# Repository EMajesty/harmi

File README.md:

Continuation of [arduchord](https://github.com/EMajesty/arduchord), now using a Raspberry Pi Pico

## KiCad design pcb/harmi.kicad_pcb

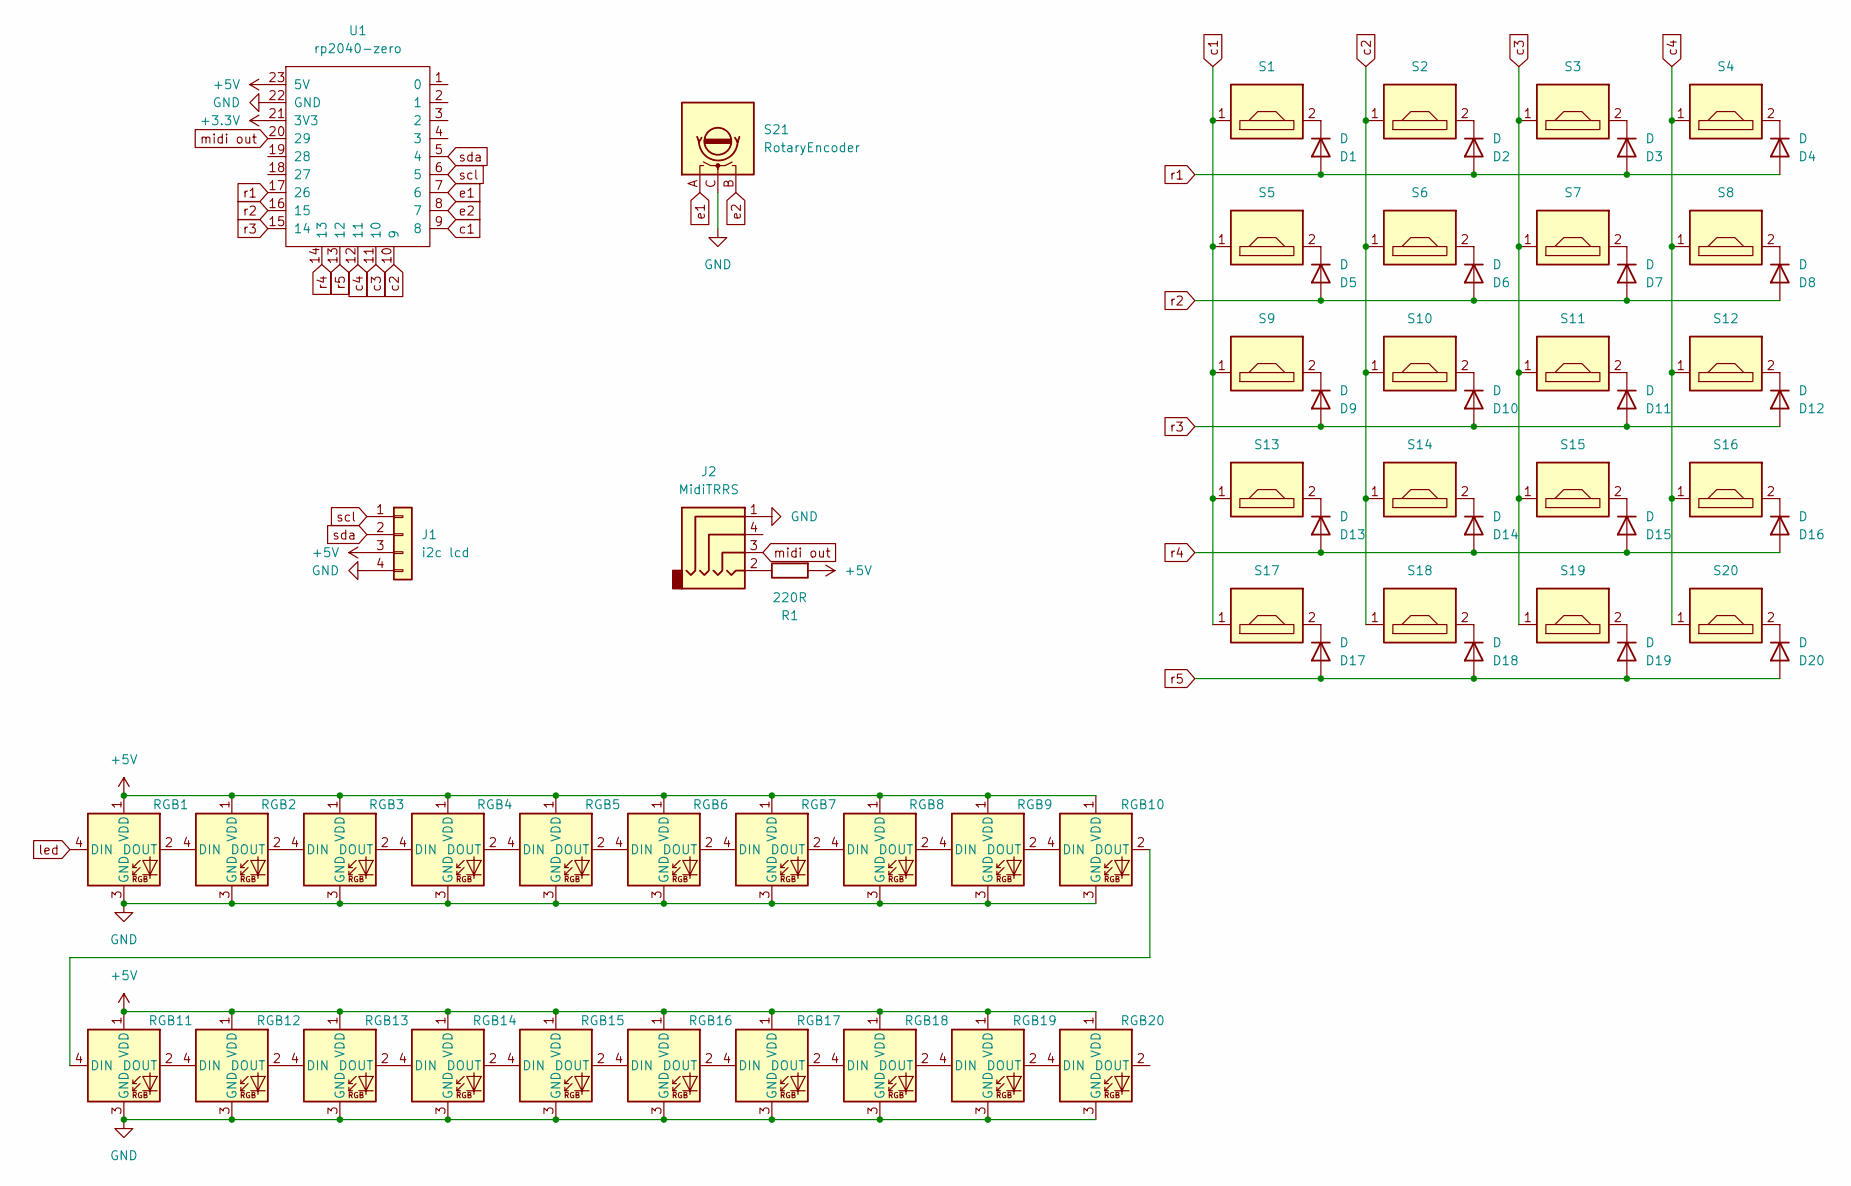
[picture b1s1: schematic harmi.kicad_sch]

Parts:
D1, D2, D3, D4, D5, D6, D7, D8, D9, D10, D11, D12, D13, D14, D15, D16, D17, D18, D19, D20: D; Diode-Hybrid-Back
J1: i2c lcd; PinHeader_1x04_P2.54mm_Horizontal
J2: MidiTRRS; TRRS-PJ-320A
R1: 220R; Resistor-Hybrid-Back
RGB1, RGB2, RGB3, RGB4, RGB5, RGB6, RGB7, RGB8, RGB9, RGB10, RGB11, RGB12, RGB13, RGB14, RGB15, RGB16, RGB17, RGB18, RGB19, RGB20: SK6812MINI-E
S1, S2, S3, S4, S5, S6, S7, S8, S9, S10, S11, S12, S13, S14, S15, S16, S17, S18, S19, S20: PG1350
S21: RotaryEncoder; RotaryEncoder_Bourns_Vertical_PEC12R-3x17F-Nxxxx
U1: rp2040-zero; rp2040-zero-tht

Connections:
+3.3V: U1.21 (3V3)
+5V: J1.3, R1.2, RGB1.1 (VDD), RGB2.1 (VDD), RGB3.1 (VDD), RGB4.1 (VDD), RGB5.1 (VDD), RGB6.1 (VDD), RGB7.1 (VDD), RGB8.1 (VDD), RGB9.1 (VDD), RGB10.1 (VDD), RGB11.1 (VDD), RGB12.1 (VDD), RGB13.1 (VDD), RGB14.1 (VDD), RGB15.1 (VDD), RGB16.1 (VDD), RGB17.1 (VDD), RGB18.1 (VDD), RGB19.1 (VDD), RGB20.1 (VDD), U1.23 (5V)
GND: J1.4, J2.1, RGB1.3 (GND), RGB2.3 (GND), RGB3.3 (GND), RGB4.3 (GND), RGB5.3 (GND), RGB6.3 (GND), RGB7.3 (GND), RGB8.3 (GND), RGB9.3 (GND), RGB10.3 (GND), RGB11.3 (GND), RGB12.3 (GND), RGB13.3 (GND), RGB14.3 (GND), RGB15.3 (GND), RGB16.3 (GND), RGB17.3 (GND), RGB18.3 (GND), RGB19.3 (GND), RGB20.3 (GND), S21.C, U1.22 (GND)
unnamed: D1.1 (K), S1.2
unnamed: D2.1 (K), S2.2
unnamed: D3.1 (K), S3.2
unnamed: D4.1 (K), S4.2
unnamed: D5.1 (K), S5.2
unnamed: D6.1 (K), S6.2
unnamed: D7.1 (K), S7.2
unnamed: D8.1 (K), S8.2
unnamed: D9.1 (K), S9.2
unnamed: D10.1 (K), S10.2
unnamed: D11.1 (K), S11.2
unnamed: D12.1 (K), S12.2
unnamed: D13.1 (K), S13.2
unnamed: D14.1 (K), S14.2
unnamed: D15.1 (K), S15.2
unnamed: D16.1 (K), S16.2
unnamed: D17.1 (K), S17.2
unnamed: D18.1 (K), S18.2
unnamed: D19.1 (K), S19.2
unnamed: D20.1 (K), S20.2
unnamed: J2.2, R1.1
unnamed: RGB1.2 (DOUT), RGB2.4 (DIN)
unnamed: RGB2.2 (DOUT), RGB3.4 (DIN)
unnamed: RGB3.2 (DOUT), RGB4.4 (DIN)
unnamed: RGB4.2 (DOUT), RGB5.4 (DIN)
unnamed: RGB5.2 (DOUT), RGB6.4 (DIN)
unnamed: RGB6.2 (DOUT), RGB7.4 (DIN)
unnamed: RGB7.2 (DOUT), RGB8.4 (DIN)
unnamed: RGB8.2 (DOUT), RGB9.4 (DIN)
unnamed: RGB9.2 (DOUT), RGB10.4 (DIN)
unnamed: RGB10.2 (DOUT), RGB11.4 (DIN)
unnamed: RGB11.2 (DOUT), RGB12.4 (DIN)
unnamed: RGB12.2 (DOUT), RGB13.4 (DIN)
unnamed: RGB13.2 (DOUT), RGB14.4 (DIN)
unnamed: RGB14.2 (DOUT), RGB15.4 (DIN)
unnamed: RGB15.2 (DOUT), RGB16.4 (DIN)
unnamed: RGB16.2 (DOUT), RGB17.4 (DIN)
unnamed: RGB17.2 (DOUT), RGB18.4 (DIN)
unnamed: RGB18.2 (DOUT), RGB19.4 (DIN)
unnamed: RGB19.2 (DOUT), RGB20.4 (DIN)
c1: S1.1, S5.1, S9.1, S13.1, S17.1, U1.9 (8)
c2: S2.1, S6.1, S10.1, S14.1, S18.1, U1.10 (9)
c3: S3.1, S7.1, S11.1, S15.1, S19.1, U1.11 (10)
c4: S4.1, S8.1, S12.1, S16.1, S20.1, U1.12 (11)
e1: S21.A, U1.7 (6)
e2: S21.B, U1.8 (7)
led: RGB1.4 (DIN)
midi out: J2.3, U1.20 (29)
r1: D1.2 (A), D2.2 (A), D3.2 (A), D4.2 (A), U1.17 (26)
r2: D5.2 (A), D6.2 (A), D7.2 (A), D8.2 (A), U1.16 (15)
r3: D9.2 (A), D10.2 (A), D11.2 (A), D12.2 (A), U1.15 (14)
r4: D13.2 (A), D14.2 (A), D15.2 (A), D16.2 (A), U1.14 (13)
r5: D17.2 (A), D18.2 (A), D19.2 (A), D20.2 (A), U1.13 (12)
scl: J1.1, U1.6 (5)
sda: J1.2, U1.5 (4)

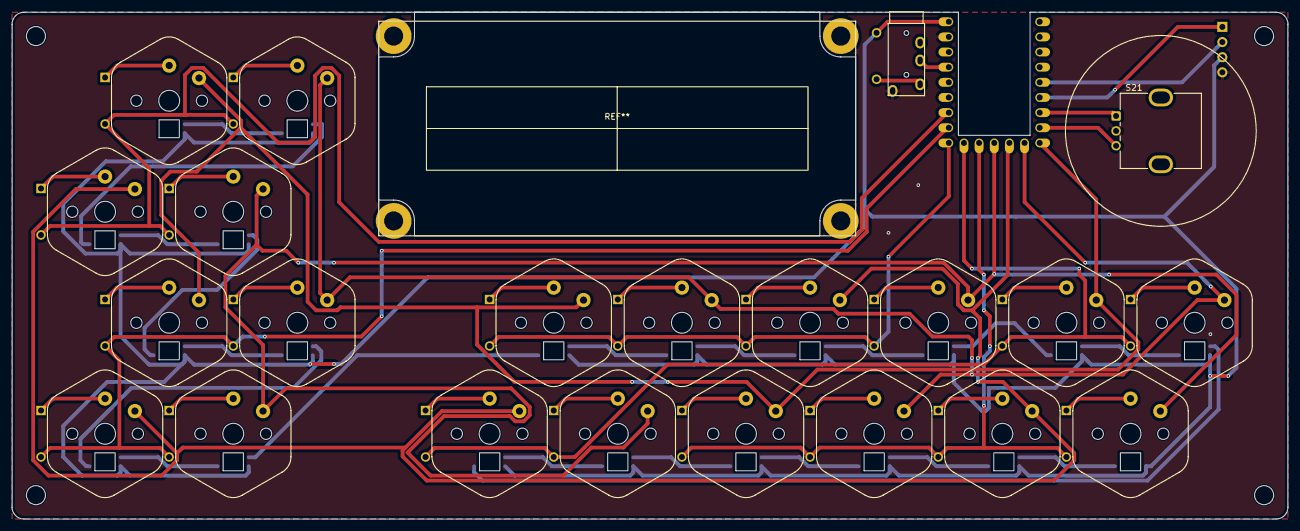
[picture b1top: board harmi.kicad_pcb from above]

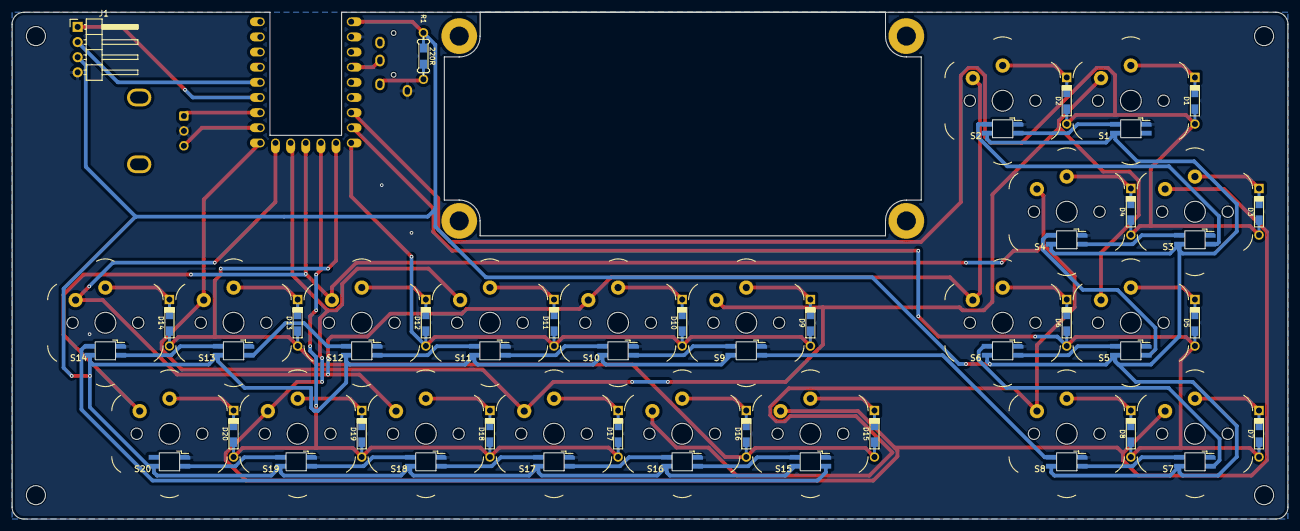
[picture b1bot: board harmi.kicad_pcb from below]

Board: 2 copper layers, 213.9 x 85.0 mm, 65 parts (21 on the bottom side), 56 nets.

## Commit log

2024-11-26 init
2024-11-26 add readme
2024-11-26 add stuff to make stuff work
2024-11-26 lcd, usb debugging
2024-11-26 usb stuff
2024-11-26 asdf
2024-11-27 switch back to platformio
2024-11-27 lcd works, midi sends
2024-11-27 update gitignore
2024-11-27 cleanup
2024-12-01 add pcb
2024-12-01 add kicad gitignore
2024-12-01 what
2024-12-01 remove gerbers
2024-12-01 structure, libs
2024-12-06 clean
2024-12-06 add forked Keypad repo as lib submodule
2024-12-07 oop shit
